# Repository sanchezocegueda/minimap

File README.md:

# Information
See our [initial project proposal](deliverables/Project_Proposal.pdf) for a high level overview of what we're building.

All artifacts can be found in [artifacts](artifacts)

All deliverables can be found in [deliverables](deliverables)

All code and example projects can be found in [esp32-prototype](esp32-prototype)
- See [esp32-prototype/DETAILS.md](esp32-prototype/DETAILS.md)

# Prototypes

### Current prototype without buttons

### Current prototype without buttons and gps (for a better visual)

# Getting started with development on a fresh machine

## Setup repo
```bash
# ssh
git clone git@github.com:sanchezocegueda/minimap.git
# http
git clone https://github.com/sanchezocegueda/minimap.git
cd minimap
git submodule update --init --recursive
```

## Setup IDF toolchain and VSCode extension
See [esp32-prototype/DEVELOPING.md](esp32-prototype/DEVELOPING.md)

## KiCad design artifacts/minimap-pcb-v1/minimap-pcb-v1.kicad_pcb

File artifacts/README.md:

[peripheral_pins.md](peripheral_pins.md) is the most accurate description of our breadboard pinout for each device

[149_Project_Doc.pdf](149_Project_Doc.pdf) is a current reflection of our high level ideas and any calculations we've done.

### circuit schematic for the breadboard, it is a little out of date

### outdated visual of how we interface with each device

### pcb we built to hopefully have more than 2 devices
- This is a backburner task, but if time permits we hope to get atleast one more device assembled using this pcb.

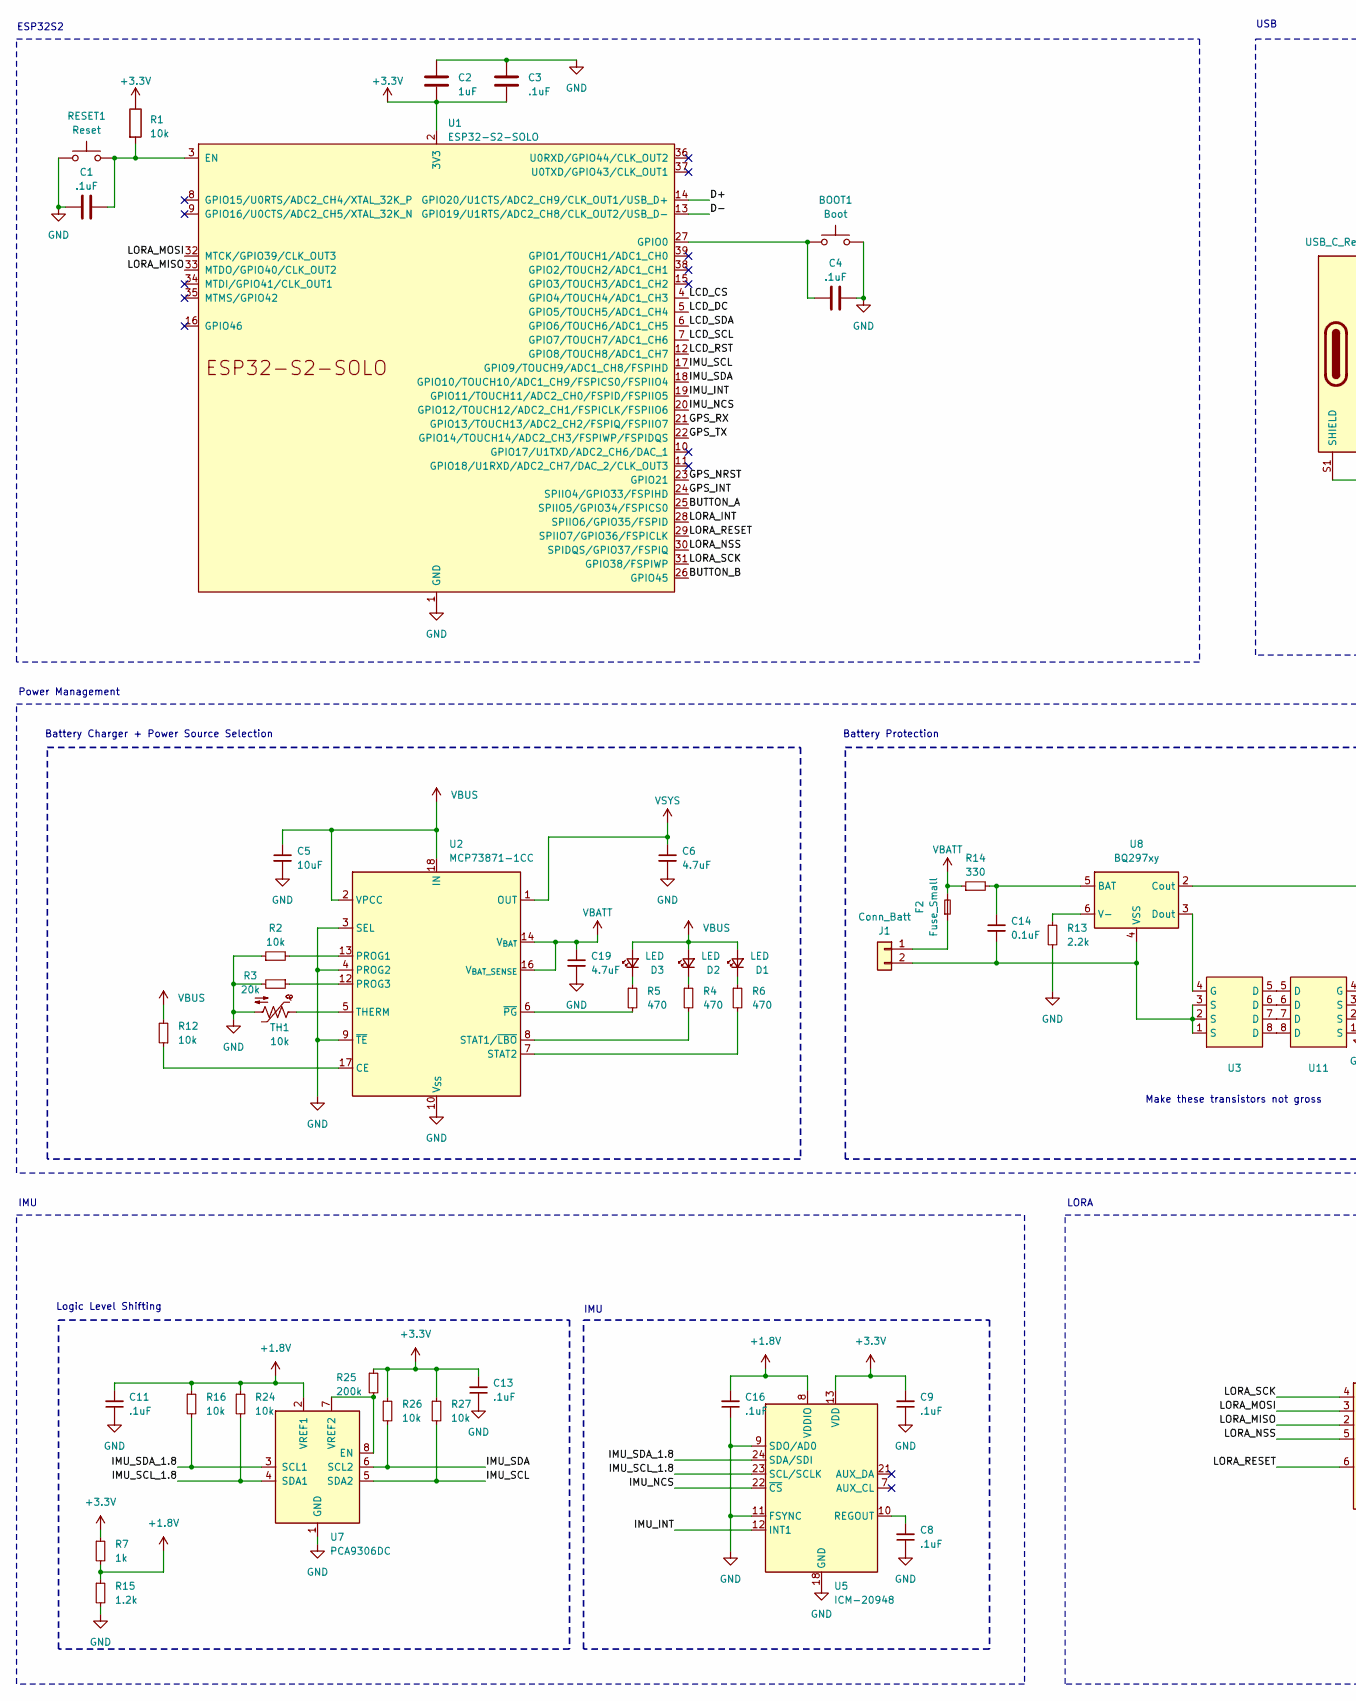
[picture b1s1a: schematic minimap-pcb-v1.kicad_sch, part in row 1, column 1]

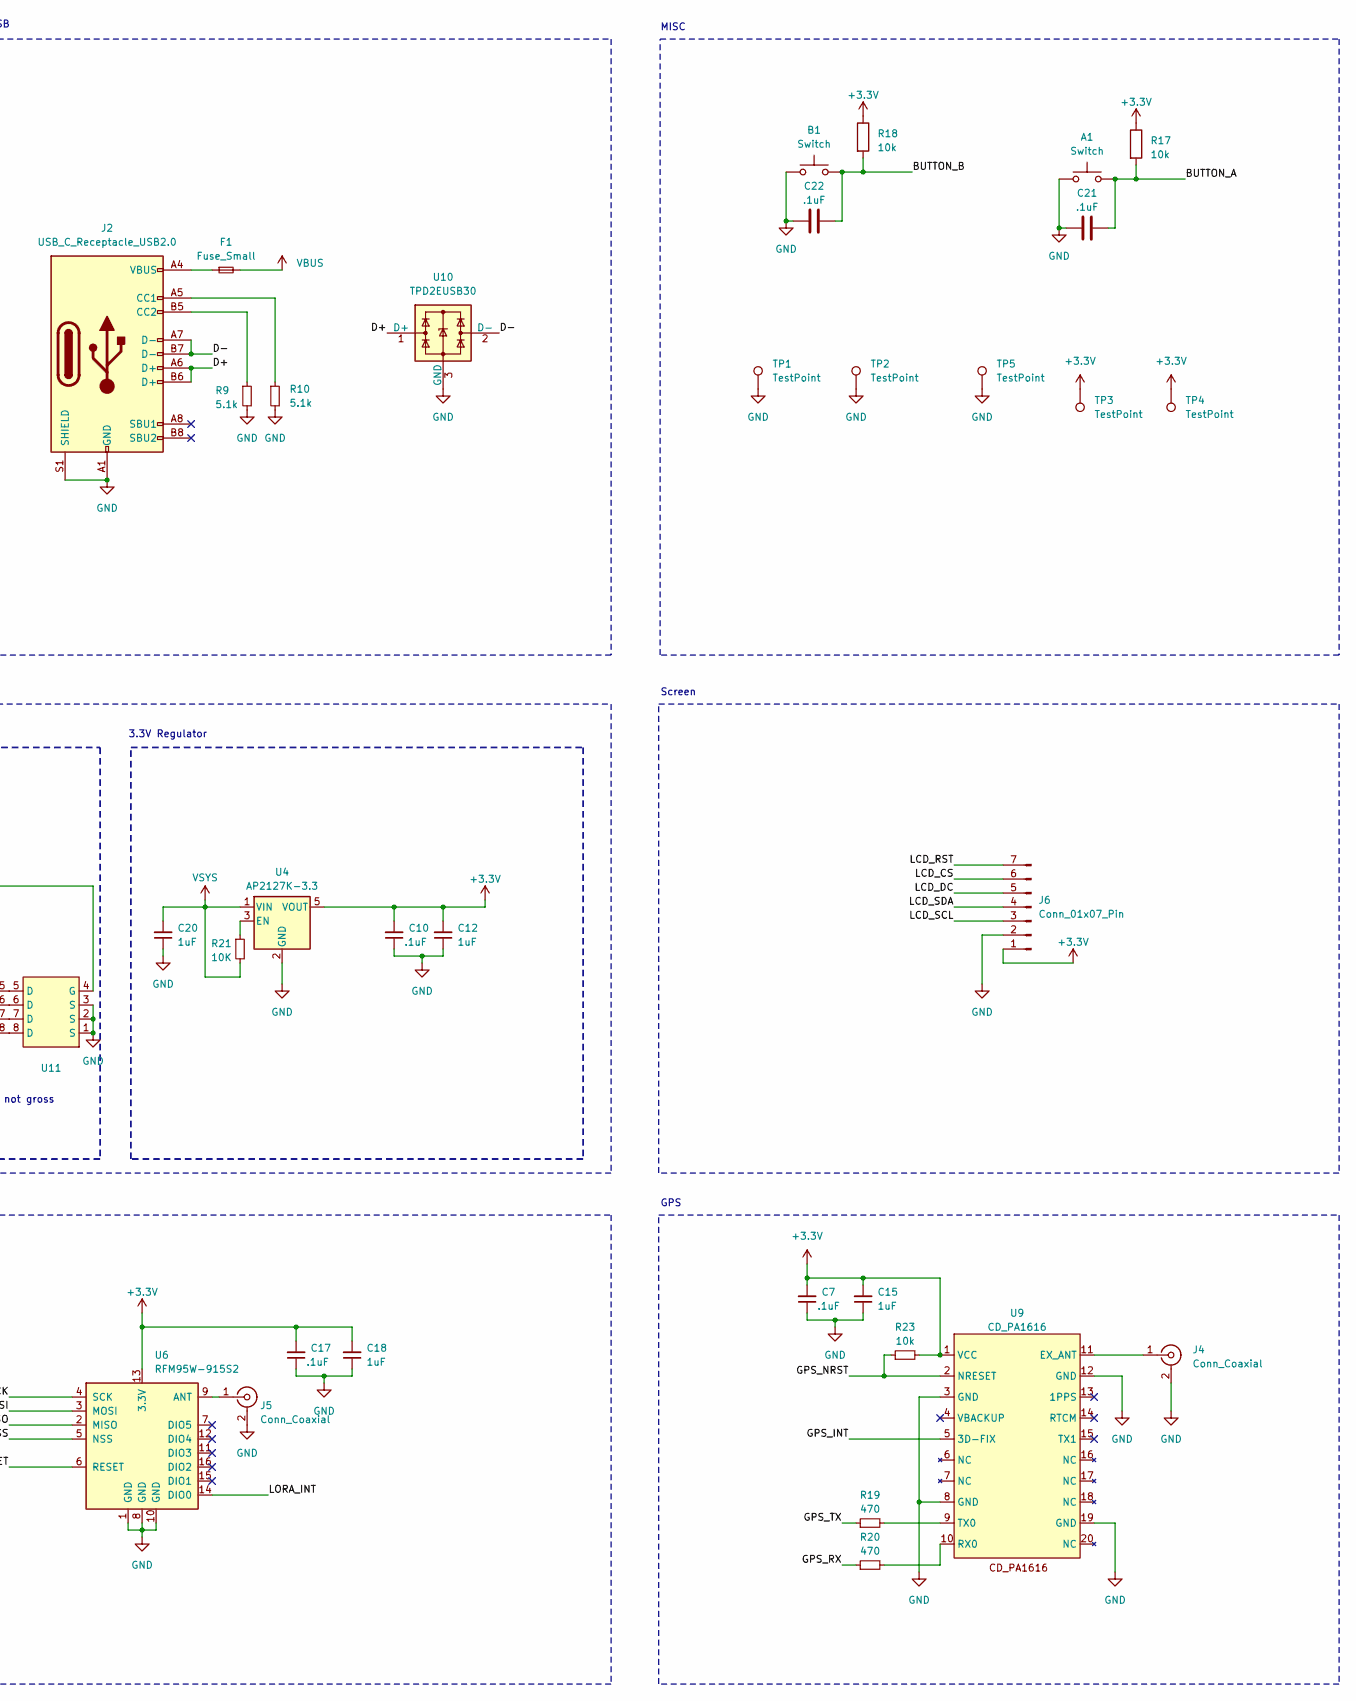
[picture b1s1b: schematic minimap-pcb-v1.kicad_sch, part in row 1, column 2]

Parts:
A1: Switch; SW_Tactile_SPST_Angled_PTS645Vx83-2LFS
B1: Switch; SW_Tactile_SPST_Angled_PTS645Vx83-2LFS
BOOT1: Boot; SW_Push_1P1T_NO_6x6mm_H9.5mm
C1, C3, C4, C7, C8, C9, C10, C11, C13, C16, C17, C21, C22: .1uF; C_0603_1608Metric
C2, C12, C15, C18, C20: 1uF; C_0603_1608Metric
C5: 10uF; C_0603_1608Metric
C6, C19: 4.7uF; C_0603_1608Metric
C14: 0.1uF; C_0603_1608Metric
D1, D2, D3: LED; LED_0603_1608Metric
F1, F2: Fuse_Small; Fuse_0603_1608Metric
J1: Conn_Batt; JST_PH_S2B-PH-K_1x02_P2.00mm_Horizontal
J2: USB_C_Receptacle_USB2.0; USB_C_Receptacle_JAE_DX07S016JA1R1500
J4, J5: Conn_Coaxial; U.FL_Molex_MCRF_73412-0110_Vertical
J6: Conn_01x07_Pin; PinHeader_1x07_P2.54mm_Vertical
R1, R2, R12, R16, R17, R18, R23, R24, R26, R27: 10k; R_0603_1608Metric
R3: 20k; R_0603_1608Metric
R4, R5, R6, R19, R20: 470; R_0603_1608Metric
R7: 1k; R_0603_1608Metric
R9, R10: 5.1k; R_0603_1608Metric
R13: 2.2k; R_0603_1608Metric
R14: 330; R_0603_1608Metric
R15: 1.2k; R_0603_1608Metric
R21: 10K; R_0603_1608Metric
R25: 200k; R_0603_1608Metric
RESET1: Reset; SW_Push_1P1T_NO_6x6mm_H9.5mm
TH1: 10k; R_0603_1608Metric
TP1, TP2: TestPoint; TestPoint_Plated_Hole_D2.0mm
TP3, TP4, TP5: TestPoint; TestPoint_Pad_D1.5mm
U1: ESP32-S2-SOLO
U2: MCP73871-1CC; QFN-20-1EP_4x4mm_P0.5mm_EP2.5x2.5mm
U3, U11: VSON-8_3.3x3.3mm_P0.65mm_NexFET
U4: AP2127K-3.3; SOT-23-5
U5: ICM-20948; InvenSense_QFN-24_3x3mm_P0.4mm
U6: RFM95W-915S2; HOPERF_RFM9XW_SMD
U7: PCA9306DC; VSSOP-8_2.3x2mm_P0.5mm
U8: BQ297xy; WSON-6_1.5x1.5mm_P0.5mm
U9: CD_PA1616; CD-PA1616D
U10: TPD2EUSB30; Texas_DRT-3

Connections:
+1.8V: C11.2, C16.2, R7.2, R15.1, R16.1, R24.1, U5.8 (VDDIO), U7.2 (VREF1)
+3.3V: C2.2, C3.2, C7.2, C9.2, C10.2, C12.2, C13.2, C15.2, C17.2, C18.2, J6.1, R1.1, R7.1, R17.1, R18.1, R23.2, R25.1, R26.1, R27.1, TP3.1, TP4.1, U1.2 (3V3), U4.5 (VOUT), U5.13 (VDD), U6.13 (3.3V), U9.1 (VCC); also elsewhere on the board
/BUTTON_A: A1.2, C21.2, R17.2, U1.25 (SPIIO5/GPIO34/FSPICS0)
/BUTTON_B: B1.2, C22.2, R18.2, U1.26 (GPIO45)
/D+: J2.A6 (D+), J2.B6 (D+), U1.14 (GPIO20/U1CTS/ADC2_CH9/CLK_OUT1/USB_D+), U10.1 (D+)
/D-: J2.A7 (D-), J2.B7 (D-), U1.13 (GPIO19/U1RTS/ADC2_CH8/CLK_OUT2/USB_D-), U10.2 (D-)
/GPS_INT: U1.24 (SPIIO4/GPIO33/FSPIHD), U9.5 (3D-FIX)
/GPS_NRST: R23.1, U1.23 (GPIO21), U9.2 (NRESET)
/GPS_RX: R20.1, U1.21 (GPIO13/TOUCH13/ADC2_CH2/FSPIQ/FSPIIO7)
/GPS_TX: R19.1, U1.22 (GPIO14/TOUCH14/ADC2_CH3/FSPIWP/FSPIDQS)
/IMU_INT: U1.19 (GPIO11/TOUCH11/ADC2_CH0/FSPID/FSPIIO5), U5.12 (INT1)
/IMU_NCS: U1.20 (GPIO12/TOUCH12/ADC2_CH1/FSPICLK/FSPIIO6), U5.22 (~CS)
/IMU_SCL: R27.2, U1.17 (GPIO9/TOUCH9/ADC1_CH8/FSPIHD), U7.5 (SDA2)
/IMU_SCL_1.8: R24.2, U5.23 (SCL/SCLK), U7.4 (SDA1)
/IMU_SDA: R26.2, U1.18 (GPIO10/TOUCH10/ADC1_CH9/FSPICS0/FSPIIO4), U7.6 (SCL2)
/IMU_SDA_1.8: R16.2, U5.24 (SDA/SDI), U7.3 (SCL1)
/LCD_CS: J6.6, U1.4 (GPIO4/TOUCH4/ADC1_CH3)
/LCD_DC: J6.5, U1.5 (GPIO5/TOUCH5/ADC1_CH4)
/LCD_RST: J6.7, U1.12 (GPIO8/TOUCH8/ADC1_CH7)
/LCD_SCL: J6.3, U1.7 (GPIO7/TOUCH7/ADC1_CH6)
/LCD_SDA: J6.4, U1.6 (GPIO6/TOUCH6/ADC1_CH5)
/LORA_INT: U1.28 (SPIIO6/GPIO35/FSPID), U6.14 (DIO0)
/LORA_MISO: U1.33 (MTDO/GPIO40/CLK_OUT2), U6.2 (MISO)
/LORA_MOSI: U1.32 (MTCK/GPIO39/CLK_OUT3), U6.3 (MOSI)
/LORA_NSS: U1.30 (SPIDQS/GPIO37/FSPIQ), U6.5 (NSS)
/LORA_RESET: U1.29 (SPIIO7/GPIO36/FSPICLK), U6.6 (RESET)
/LORA_SCK: U1.31 (GPIO38/FSPIWP), U6.4 (SCK)
GND: A1.1, B1.1, BOOT1.2, C1.1, C2.1, C3.1, C4.2, C5.2, C6.2, C7.1, C8.1, C9.1, C10.1, C11.1, C12.1, C13.1, C15.1, C16.1, C17.1, C18.1, C19.2, C20.1, C21.1, C22.1, J2.A1 (GND), J2.A12 (GND), J2.B1 (GND), J2.B12 (GND), J2.S1 (SHIELD), J4.2 (Ext), J5.2 (Ext), J6.2, R2.1, R3.2, R9.2, R10.2, R13.2, R15.2, RESET1.1, TH1.2, TP1.1, TP2.1, TP5.1, U1.1 (GND), U1.40 (GND), U1.41 (GND), U2.3 (SEL), U2.4 (PROG2), U2.9 (~TE), U2.10 (V_{SS}), U2.11 (V_{SS}), U2.21 (V_{SS}), U4.2 (GND), U5.9 (SDO/AD0), U5.11 (FSYNC), U5.18 (GND), U5.20 (GND), U6.1 (GND), U6.8 (GND), U6.10 (GND), U7.1 (GND), U9.3 (GND), U9.8 (GND), U9.12 (GND), U9.19 (GND), U10.3 (GND), U11.1 (S), U11.2 (S), U11.3 (S); also elsewhere on the board
unnamed: D1.1 (K), R6.1
unnamed: D2.1 (K), R4.1
unnamed: D3.1 (K), R5.1
unnamed: F1.1, J2.A4 (VBUS), J2.A9 (VBUS), J2.B4 (VBUS), J2.B9 (VBUS)
unnamed: F2.1, J1.1
unnamed: C14.2, J1.2, U3.1 (S), U3.2 (S), U3.3 (S), U8.4 (VSS)
unnamed: J2.A5 (CC1), R10.1
unnamed: J2.B5 (CC2), R9.1
unnamed: J4.1 (In), U9.11 (EX_ANT)
unnamed: J5.1 (In), U6.9 (ANT)
unnamed: C1.2, R1.2, RESET1.2, U1.3 (EN)
unnamed: BOOT1.1, C4.1, U1.27 (GPIO0)
unnamed: R12.1, U2.17 (CE)
unnamed: R2.2, U2.13 (PROG1)
unnamed: R3.1, U2.12 (PROG3)
unnamed: R4.2, U2.8 (STAT1/~LBO)
unnamed: R6.2, U2.7 (STAT2)
unnamed: TH1.1, U2.5 (THERM)
unnamed: R5.2, U2.6 (~PG)
unnamed: U3.4 (G), U8.3 (Dout)
unnamed: R21.1, U4.3 (EN)
unnamed: C8.2, U5.10 (REGOUT)
unnamed: R25.2, U7.7 (VREF2), U7.8 (EN)
unnamed: C14.1, R14.2, U8.5 (BAT)
unnamed: R13.1, U8.6 (V-)
unnamed: R20.2, U9.10 (RX0)
unnamed: R19.2, U9.9 (TX0)
unnamed: U3.5 (D), U11.5 (D)
unnamed: U8.2 (Cout), U11.4 (G)
VBATT: C19.1, F2.2, R14.1, U2.14 (V_{BAT}), U2.15 (V_{BAT}), U2.16 (V_{BAT_SENSE})
VBUS: C5.1, D1.2 (A), D2.2 (A), D3.2 (A), F1.2, R12.2, U2.2 (VPCC), U2.18 (IN), U2.19 (IN)
VSYS: C6.1, C20.2, R21.2, U2.1 (OUT), U2.20 (OUT), U4.1 (VIN)

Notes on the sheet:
Screen
IMU
Battery Charger + Power Source Selection
Battery Protection
Make these transistors not gross
ESP32S2
Power Management
LORA
GPS
3.3V Regulator
Logic Level Shifting
USB
MISC

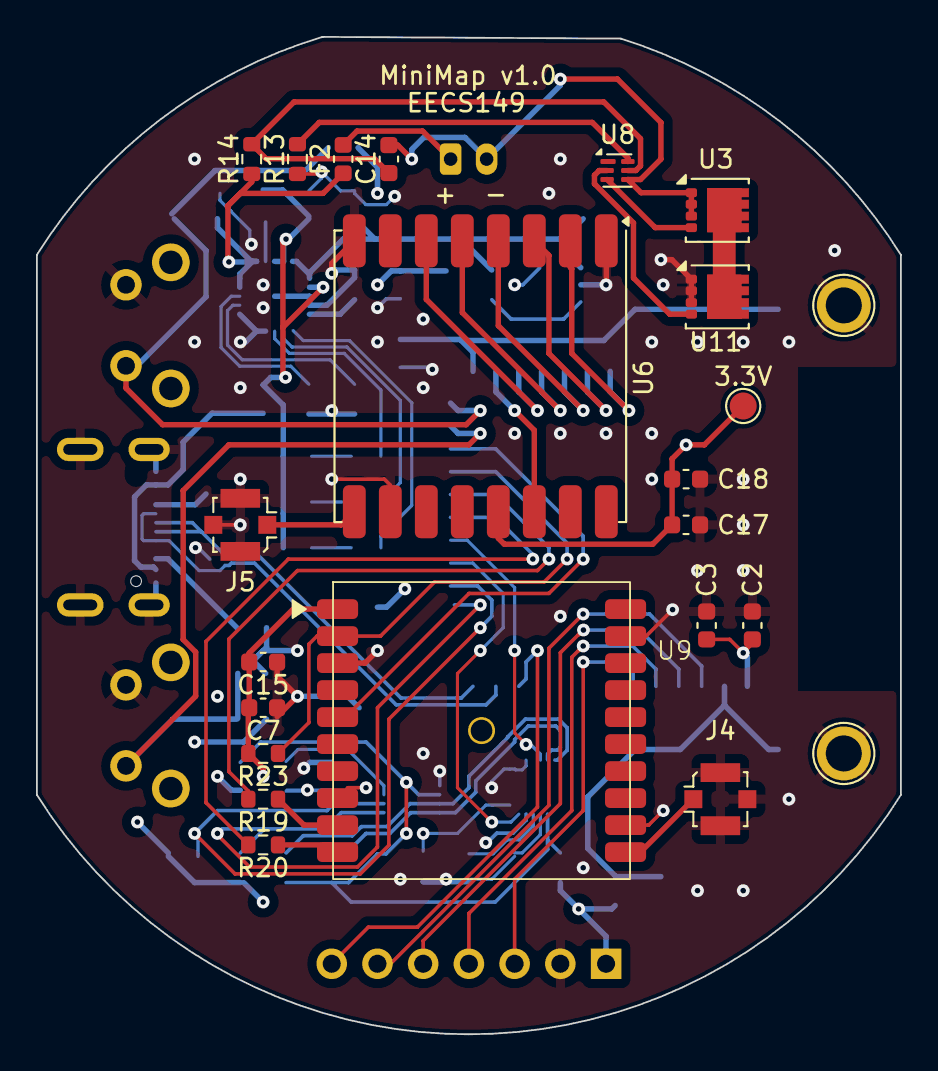
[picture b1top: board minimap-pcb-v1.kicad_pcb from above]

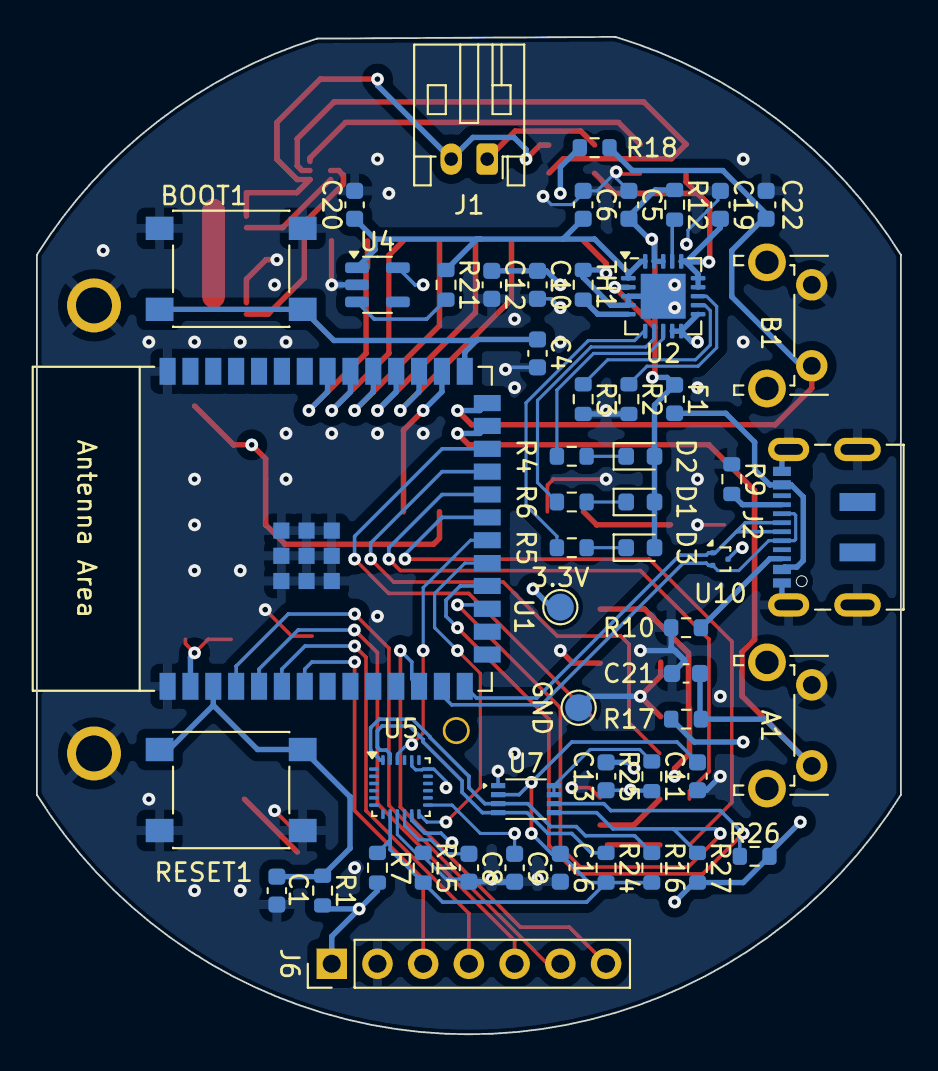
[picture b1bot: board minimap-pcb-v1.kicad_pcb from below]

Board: 4 copper layers, 48.0 x 55.4 mm, 77 parts (54 on the bottom side), 60 nets.

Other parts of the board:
3.3V, 3.3V#2: TestPoint; TestPoint_Pad_D1.5mm
GND: TestPoint; TestPoint_Pad_D1.5mm

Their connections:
+3.3V: 3.3V.1, 3.3V#2.1; also elsewhere on the board
GND: GND.1; also elsewhere on the board

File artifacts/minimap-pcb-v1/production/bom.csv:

Designator,Footprint,Quantity,Value,LCSC Part #
"3.3V_2, 3.3V, GND",TestPoint_Pad_D1.5mm,3,TestPoint,
"A1, B1",SW_Tactile_SPST_Angled_PTS645Vx83-2LFS,2,Switch,
BOOT1,SW_Push_1P1T_NO_6x6mm_H9.5mm,1,Boot,
"C1, C10, C11, C13, C16, C17, C21, C22, C3, C4, C7, C8, C9",0603,13,.1uF,
"C12, C15, C18, C2, C20",0603,5,1uF,
C14,0603,1,0.1uF,
"C19, C6",0603,2,4.7uF,
C5,0603,1,10uF,
"D1, D2, D3",0603,3,LED,
"F1, F2",0603,2,Fuse_Small,
J1,JST_PH_S2B-PH-K_1x02_P2.00mm_Horizontal,1,Conn_Batt,
J2,USB_C_Receptacle_JAE_DX07S016JA1R1500,1,USB_C_Receptacle_USB2.0,
"J4, J5",U.FL_Molex_MCRF_73412-0110_Vertical,2,Conn_Coaxial,
J6,PinHeader_1x07_P2.54mm_Vertical,1,Conn_01x07_Pin,
"R1, R12, R16, R17, R18, R2, R21, R23, R24, R26, R27, TH1",0603,12,10k,
"R10, R9",0603,2,5.1k,
R13,0603,1,2.2k,
R14,0603,1,330,
R15,0603,1,1.2k,
"R19, R20, R4, R5, R6",0603,5,470,
R25,0603,1,200k,
R3,0603,1,20k,
R7,0603,1,1k,
RESET1,SW_Push_1P1T_NO_6x6mm_H9.5mm,1,Reset,
"TP1, TP2",TestPoint_Plated_Hole_D2.0mm,2,TestPoint,
U1,ESP32-S2-SOLO,1,ESP32-S2-SOLO,
U10,Texas_DRT-3,1,TPD2EUSB30,
"U11, U3",VSON-8_3.3x3.3mm_P0.65mm_NexFET,2,~,
U2,QFN-20-1EP_4x4mm_P0.5mm_EP2.5x2.5mm,1,MCP73871-1CC,
U4,SOT-23-5,1,AP2127K-3.3,
U5,InvenSense_QFN-24_3x3mm_P0.4mm,1,ICM-20948,
U6,HOPERF_RFM9XW_SMD,1,RFM95W-915S2,
U7,VSSOP-8_2.3x2mm_P0.5mm,1,PCA9306DC,
U8,WSON-6_1.5x1.5mm_P0.5mm,1,BQ297xy,
U9,CD-PA1616D,1,CD_PA1616,

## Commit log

2024-10-29 add readme
2024-11-07 begin pico-prototype
    Add a basic configuration similar to the lf-pi repo from lab for
    prototyping with a pico-w
2024-11-07 Added luca's datasheets and notes
2024-11-07 Starting to work on and research esp32-idf framework
    Added my up to date notes
2024-11-08 esp IDF research
2024-11-08 add lcd example
2024-11-08 Getting started with esp-idf
2024-11-09 initial pinout descriptions
2024-11-09 fix typo
2024-11-09 addtional pinout info
2024-11-09 Updated markdown files to render nice
2024-11-09 format markdown
2024-11-09 Hardware artifacts added
2024-11-09 Add handwritten notes
2024-11-09 Remove old pinout diagram
2024-11-09 Update documentation for esp32-prototype
2024-11-09 fix github rendering links
2024-11-09 Refactor some things and add dependency graph whiteboard sketch
2024-11-10 Update .gitignore to exclude managed_components folder
2024-11-10 Pull in updated lcd example from esp-idf
2024-11-10 Basic config for spi_lcd_touch
    This has not been tested, but compiles
2024-11-10 Put the correct hardware driver in sdkconfig.defaults
2024-11-10 Copied .gitignore from esp-idf repo
    For now it seems sdkconfig is something included in vcs, if for some reason you have difficulty
    building the spi_lcd example, perhaps delete it and try again.
2024-11-10 remove testing directory and added information about libraries
2024-11-10 simple radiolib example filled out
2024-11-10 Added TODO.md with integration tasks
2024-11-10 project init with mpu9250 component from registry
2024-11-10 moved the imu example from the library and setup pins
2024-11-10 Added blink example and updated docs
2024-11-12 modified the example slightly
2024-11-12 gps library compiling
    need to write an example
2024-11-13 both imus work
    lora radio transmitting hello world
2024-11-13 more functionality for the screen
2024-11-13 Added nmea0183_parser from esp-idf examples
    Updated TODO.md
2024-11-13 Added interrupt links to imu example
2024-11-14 four fake ppl on minimap screen
2024-11-14 update TODO.md with screen tasks
2024-11-14 minor update to TODO.md
2024-11-15 GPS NMEA parser working
    setup hardware_integration program and it compiles
2024-11-17 added screen api
2024-11-18 screen task updating
2024-11-18 removed imu submodule
2024-11-18 removing folders
2024-11-18 moved submodules into local
2024-11-18 new IMU library
2024-11-18 IMU and GPS in hardware_integration
2024-11-18 IMU/GPS/SCREEN demo working in esp32-prototype/SCREEN_IMU_GPS
    moved some old examples to .old directory in esp32-prototype
2024-11-19 receive i.p
2024-11-20 simplier lora esp-idf component
2024-11-20 lora counter around cory
2024-11-20 draft for interrupt support in lora library
2024-11-20 lora gps transmit
2024-11-20 interrupt tx/rx counter example
2024-11-20 basic gps RX/TX over lora
2024-11-25 hardware_integration refactors with new Lora library
    adding support for hardware interrupts on the MPU9250 and
    RFM9X
    added some datasheets and updated TODO.md
2024-11-25 imu interrupt testing
2024-11-26 updating
2024-11-26 found a (rudimentary) way to pass data to screen
2024-11-26 cleanup lvgl names and add some functionality for drawing elements on screen
2024-11-26 in progress
2024-11-26 end of morning work session
2024-11-27 1st demo board drafted (w/o buttons), some GPIO pins were switched around
    researching Fusion algorithm library for IMUs
2024-11-27 synced prototype with alex/cleanup and luca's work
2024-11-28 initial prototype refactor and added README.md for each idf project
    I want to switch to storing all source files for the idf components in
    esp32-prototype/components/, for now they are copied
2024-11-28 fix TODO.md rendering
2024-12-01 bug fix
2024-12-02 Moved components into esp32-prototype/components
2024-12-02 screen component draft
2024-12-02 screen component refactor, original demos working
2024-12-03 added code for displaying campanile and sather gate to ui.c (not yet tested)
2024-12-03 updated pins for buttons
2024-12-03 Get Alex's code compiling and added CORY_DOORS data
2024-12-03 Refactor gps event loop to have multiple event IDs so different tasks can receive from the same queue and each time the GPS posts, it just posts for each event ID
2024-12-04 updated datasheets and removed pico-prototype
2024-12-04 compass tested
2024-12-05 adjust positions based on offset angle
2024-12-05 update repo to reflect state of project
2024-12-05 make documentation a little prettier
2024-12-05 event prettier
2024-12-05 added pcb
2024-12-05 added project proposal
2024-12-06 removed in progress work
2024-12-08 remove sdkconfig from .gitignore, hopefully make commits easier to read
2024-12-08 trying to get other gps modules to work, moved GPS RX pin to 33
2024-12-08 move screen into esp32-prototype/components directly, screen_component can still be used for development
2024-12-08 hardware_integration refactor, added buttons component
2024-12-08 removed unused code for final development
2024-12-08 removed lora reset because we hard wired RST together
2024-12-08 actually updated hardware_integration...
2024-12-08 added untested changes to buttons
2024-12-10 task_both for counter ironed out
2024-12-10 gps both example, can get stuck in TX/TX state
2024-12-10 fixed adjust_offsets
2024-12-10 Add PCB artifacts
2024-12-10 minimap_security added for testing mbedtls psa
2024-12-11 air530 manual added, configured gps for GLL and air530 to use multiple satellites
2024-12-11 WIP North Indicator
2024-12-11 Add minimum display distance for bubbles
2024-12-11 Cleanup ui
2024-12-11 Update labels
2024-12-11 Formatting
2024-12-11 Clean up screen library
2024-12-11 Clean up screen task
2024-12-11 Scuffed v0 demo
2024-12-11 added some notes and comments for how lora library configures hardware currently
2024-12-11 update datasheets with nmea protocol and schematic, and update peripheral_pins.md to reflect new GPS module
2024-12-11 added gkc interface pdf, maybe good to cross reference with air530_manual
2024-12-13 remove event loops from nmea_parser and use mutex instead
2024-12-13 just have one idf project
2024-12-13 actually add components
2024-12-13 Got connection between screen and lora
2024-12-13 remove old artifacts from previous commit
2024-12-13 cleaned up render_counter to use a queue on the heap and some other refactoring
    this builds, but will likely have runtime errors when flashed
2024-12-13 swapped int counter for a struct that contains the counter and a boolean flag
2024-12-13 calibration screen in progress
2024-12-15 added lvgl_timer_task, cleaned up calibration ui mostly
2024-12-15 so cooked
2024-12-15 made queues global
    add a polling window for receiving in task_both
2024-12-15 lora hardware config drafts
2024-12-15 counter rx/tx with 500ms period
2024-12-15 add time on air calculations lora
2024-12-15 in progress fix calibration
2024-12-15 made sure lvgl_timer_task dies before screen_main_task is spawned -- no screen concurrency issues
2024-12-16 Created task_both that uses gps time
2024-12-16 Should theoretically be a working prototype
2024-12-16 late night changes
2024-12-16 bug fixes
2024-12-16 calibration menu spawning and killing correctly
2024-12-16 fixed screen refresh rate
2024-12-16 curr_pos and other_pos are both global variables. added handling of invalid gps readings
2024-12-17 fixed draw_north_indicator
2024-12-17 Fix IMU calibration
2024-12-17 Calibration UI fix, update default calibration
2024-12-17 initial prompt for user (calibrate?)
2024-12-17 lora.c interrupt interface cleanup
2024-12-17 interrupt lora rx/tx working
2024-12-17 swap buttons
2024-12-17 Turn off screen backlight when at rest
2024-12-17 change color of north to red
2024-12-17 fixed rendering speed and heading
2024-12-17 changed other person's color to green
2024-12-17 fix accidental redeclaration of draw_bubble
2024-12-17 remove cory doors; optimize bubble drawing
2024-12-17 v0_final_final_donotchange(2)
2024-12-17 change cory doors to appear as yellow
